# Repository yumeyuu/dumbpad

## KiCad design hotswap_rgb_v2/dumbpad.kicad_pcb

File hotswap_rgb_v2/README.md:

# dumbpad - Hotswap - RGB v2 (aka v4.x)

Originally Designed by [deveth0](https://www.github.com/deveth0).  
Modified by [yumeyuuu](https://github.com/yumeyuu) to fits RP2040 core board.   
Compatible board is [Rpi Pico](https://www.raspberrypi.com/documentation/microcontrollers/raspberry-pi-pico.html) or its clone.

## Description

Version of the original dumbpad that features Kailh Hotswap Sockets and (optional) RGB per-key lightning.  
Modified with additional EEPROM and OLED Screen

### Revisions

- 4.0 Initial file

#### dumbpad v4.0

#### Renders

### Bill of materials

| Qty   | Component     | Values             | Footprint        | Location      | Remarks                       |
| ---:  | :---          | :---               | :---             | :---          | :---:                         |
| 3     | Capacitor     | CAP 0.1u X7R 16V   | SMD 0603         | C1 - C3       |                               |
| 17    | Diodes        | 1N4148W            | SMD SOD123       | D1 - D17      |                               |
| 2     | LED           | Any Colors         | SMD LED 0603     | DL1, DL2      | Original layer indicator LED  |
| 1     | LED           | Any Colors         | SMD LED 0603     | DL3           | Original Numlock status LED   |
| 16    | LED           | SK6812MINI-E       | SK6812MINI-E     | LED1-LED16    | Optional                      |
| 1     | Processor     | RPi Pico           | Rpi Pico Pads    | M1            |                               |
| 1     | OLED Display  | 0.91" OLED Display | 2.54mm Scoket    | M2            |                               |
| 1     | NMOS          | 2N7002             | SOT-23           | Q1            | SK6812 Logic Level Shifter    |
| 3     | Resistor      | RES 1k             | SMD 0603         | R1 - R3       |                               |
| 1     | Resistor      | RES 0 (jumper)     | SMD 0603         | R4            | Bypass resistor               |
| 5     | Resistor      | RES 10k            | SMD 0603         | R5 - R9       | Optional                      |
| 1     | Encoder       | EC11 Rotary Encoder| 7 pins encoder   | RE_3_1        | Any EC11 Compatible OK        |
| 16    | KB-Socket     | Kailh Socket       | Kailh socket     | S1 - S16      |                               |
| 1     | Push Btn      | Alps SKRK          | ALPS SKRK        | S17           |                               |
| 1     | EEPROM        | 24LC32             | SOIC-8           | U1            |                               |
| 1     | Logic IC      | 74LVC2GU04GW       | SC-70            | U2            | Logic Level shifter           |

## Making the PCB

Submit either the KiCad `.kicad_pcb` or the gerber files to your prefered PCB manufacturer.  
Ensure your preffered PCB manufacturer able to process:
- Track Clearance 0.127 mm (5 mils)
- Track Width 0.127 mm (5 mils)
- Min Hole 0.3 mm 
- PCB size 1.6 mm (Common PCB size)

Prebuild gerber file located on the [gerber](gerber/) folder or file [hotswap_rgb_v2-gerber.zip](hotswap_rgb_v2-gerber.zip)

## Opening the design file

The design was created using KiCad 7.0.10 and should be compatible with later iteration.  
Using old version below 7.0 is not tested and probably not supported or could cause problem on the design.
Some of the footprint were not available on the standard KiCad library and hence available on the folder [dumbpad.pretty](dumbpad.pretty/).

### Notes on soldering

- Note 1:
This version uses SMD component, if You are unfamiliar with SMD component.  
Start with lowest possible temperature where Your solder wire can melt properly, and increase the temperature gradually until its flow easily on the solder pads.  
DON'T use high temperature or prolonged soldering time when doing the soldering. Otherwise, You may damage the component or melt the PCB lamination.  

- Note 2:
When soldering the socket and the LED it is recommended to use 360 degree C or as close as possible to this temperature.  
Especially when using Lead-Free solder alloy, its very critical to use lowest temperature where solder alloy can melt and flow easily.  
On my case 355 degree C is good temperature where the solder wire can melt easily and i have sufficient time to get best solder pads wetting.  

- Note 3:
The SK6812 LED plastic case, is very susceptible to melting! Use small solder tip and touch the PCB pads instead of the LED leads (Hakko BC-2 or similar should be good).  
Sometimes it is hard for solder alloy to wet the SK6812 LED lead frame, don't force high temperature or long soldering time!  
Instead, use some flux or clean the soldering area with IPA beforehand.  
On my build i saw some if some of the lead is not get enough solder wetting but i check with multimeter the soldering seems to be have connection. 
I suspect this due to poor storage of the SK6812 LED. (I just put in on the ESD bag with small desiccant, which probably not enough).  

- Note 4:
The SK6812 LED Pads were modified to include little chamfer to indicate GND Pin (Pin 3).

*WARNING:* 
Take a good look at the the orientation of the LEDs! 
The LED orientation changes with changes of the ROW! 

## Acknowledgements

Some of the footprints are extracted from the awesome [Corne Keyboard](https://github.com/foostan/crkbd) by [Kosuke Adachi](https://github.com/foostan).

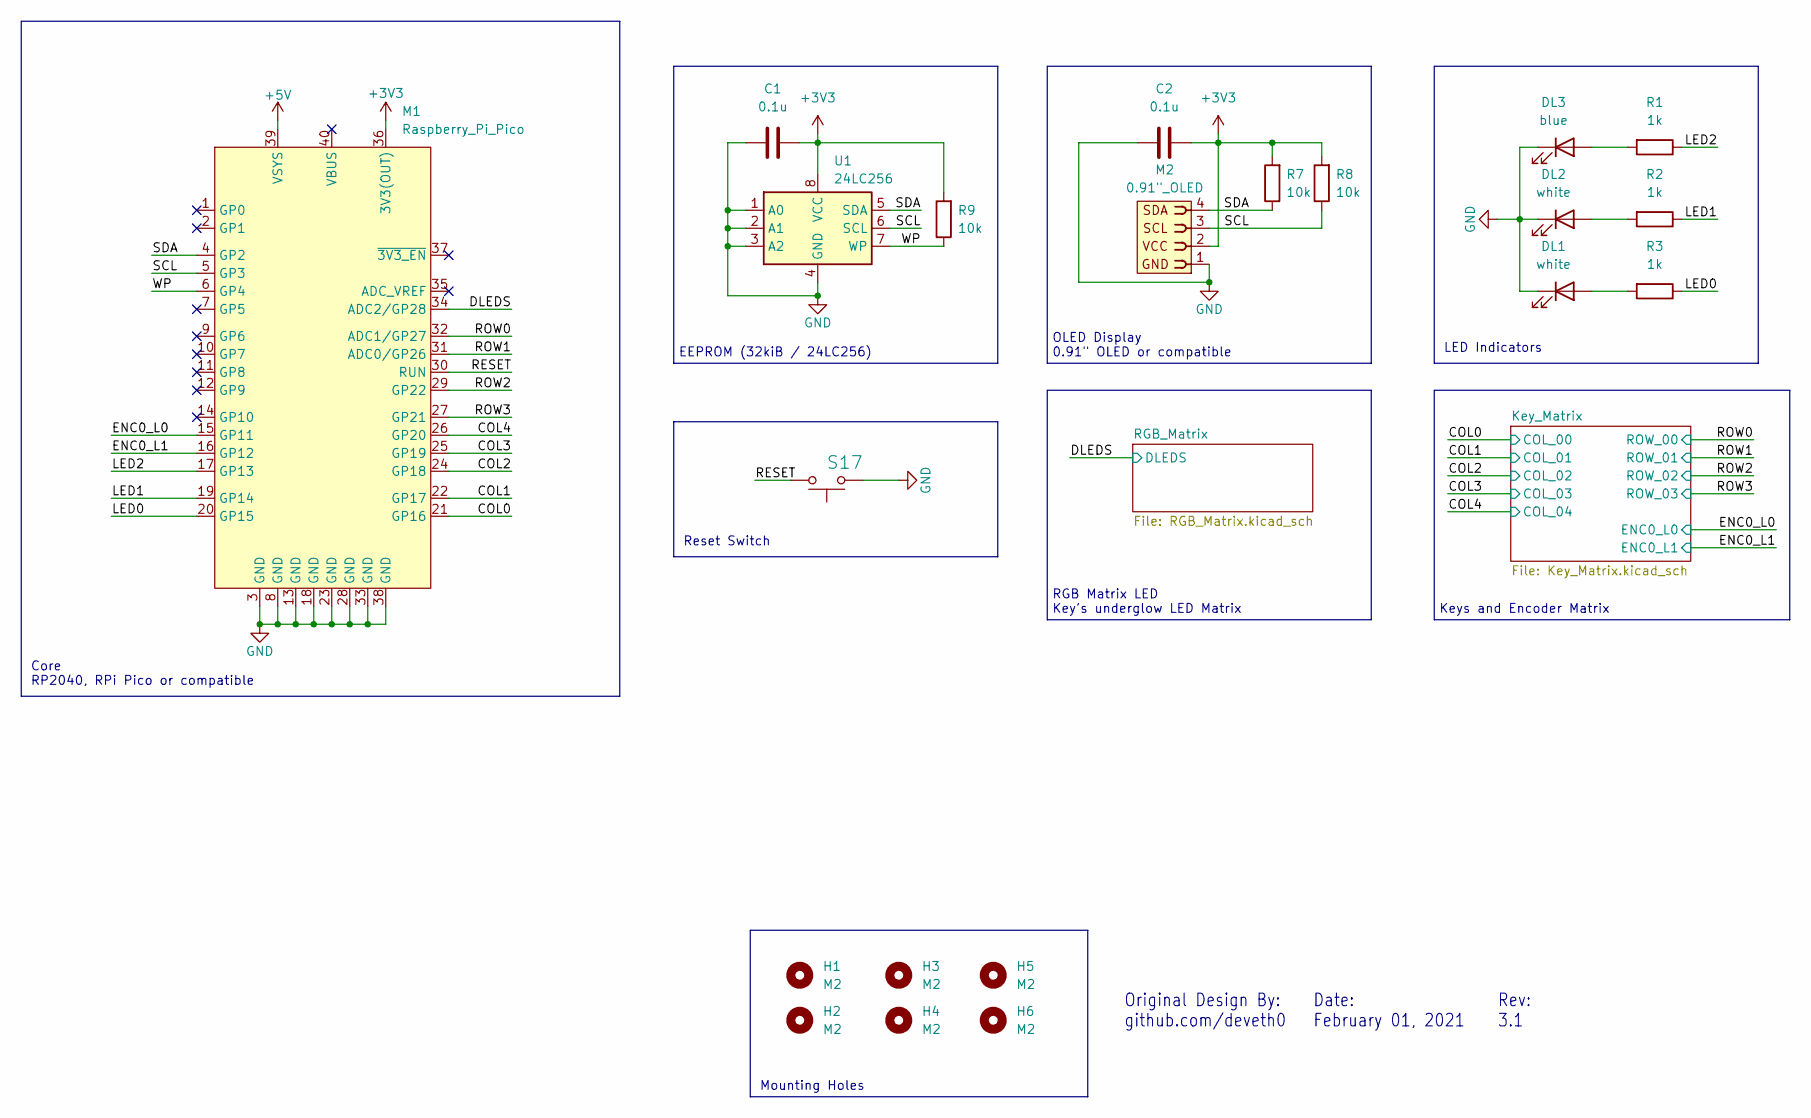
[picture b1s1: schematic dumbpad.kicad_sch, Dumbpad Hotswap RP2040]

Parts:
C1, C2: 0.1u; C_0603_1608Metric
DL1, DL2: white; LED_0603_1608Metric
DL3: blue; LED_0603_1608Metric
H1, H2, H3, H4, H5, H6: M2; MountingHole_2.2mm_M2_DIN965
M1: Raspberry_Pi_Pico; raspberry_pi_pico_THT
M2: 0.91"_OLED; PinSocket_1x04_P2.54mm_Vertical
R1, R2, R3: 1k; R_0603_1608Metric
R7, R8, R9: 10k; R_0603_1608Metric
S17: SPST Push Button; SW_Push_SPST_NO_Alps_SKRK
U1: 24LC256; SOIC-8_3.9x4.9mm_P1.27mm

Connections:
+3V3: C1.1, C2.1, M1.36 (3V3(OUT)), M2.2, R7.2, R8.2, R9.2, U1.8 (VCC); also elsewhere on the board
+5V: M1.39 (VSYS); also elsewhere on the board
/COL0: M1.21 (GP16); also elsewhere on the board
/COL1: M1.22 (GP17); also elsewhere on the board
/COL2: M1.24 (GP18); also elsewhere on the board
/COL3: M1.25 (GP19); also elsewhere on the board
/COL4: M1.26 (GP20); also elsewhere on the board
/DLEDS: M1.34 (ADC2/GP28); also elsewhere on the board
/ENC0_L0: M1.15 (GP11); also elsewhere on the board
/ENC0_L1: M1.16 (GP12); also elsewhere on the board
/LED0: M1.20 (GP15), R3.1
/LED1: M1.19 (GP14), R2.1
/LED2: M1.17 (GP13), R1.1
/RESET: M1.30 (RUN), S17.2
/ROW0: M1.32 (ADC1/GP27); also elsewhere on the board
/ROW1: M1.31 (ADC0/GP26); also elsewhere on the board
/ROW2: M1.29 (GP22); also elsewhere on the board
/ROW3: M1.27 (GP21); also elsewhere on the board
/SCL: M1.5 (GP3), M2.3, R8.1, U1.6 (SCL)
/SDA: M1.4 (GP2), M2.4, R7.1, U1.5 (SDA)
/WP: M1.6 (GP4), R9.1, U1.7 (WP)
GND: C1.2, C2.2, DL1.1 (K), DL2.1 (K), DL3.1 (K), M1.3 (GND), M1.8 (GND), M1.13 (GND), M1.18 (GND), M1.23 (GND), M1.28 (GND), M1.33 (GND), M1.38 (GND), M2.1, S17.1, U1.1 (A0), U1.2 (A1), U1.3 (A2), U1.4 (GND); also elsewhere on the board
unnamed: DL1.2 (A), R3.2
unnamed: DL2.2 (A), R2.2
unnamed: DL3.2 (A), R1.2

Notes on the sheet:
OLED Display 0.91" OLED or compatible
Keys and Encoder Matrix
Rev: 3.1
Core RP2040, RPi Pico or compatible
Original Design By: github.com/deveth0
LED Indicators
RGB Matrix LED Key's underglow LED Matrix
EEPROM (32kiB / 24LC256)
Reset Switch
Mounting Holes
Date: February 01, 2021

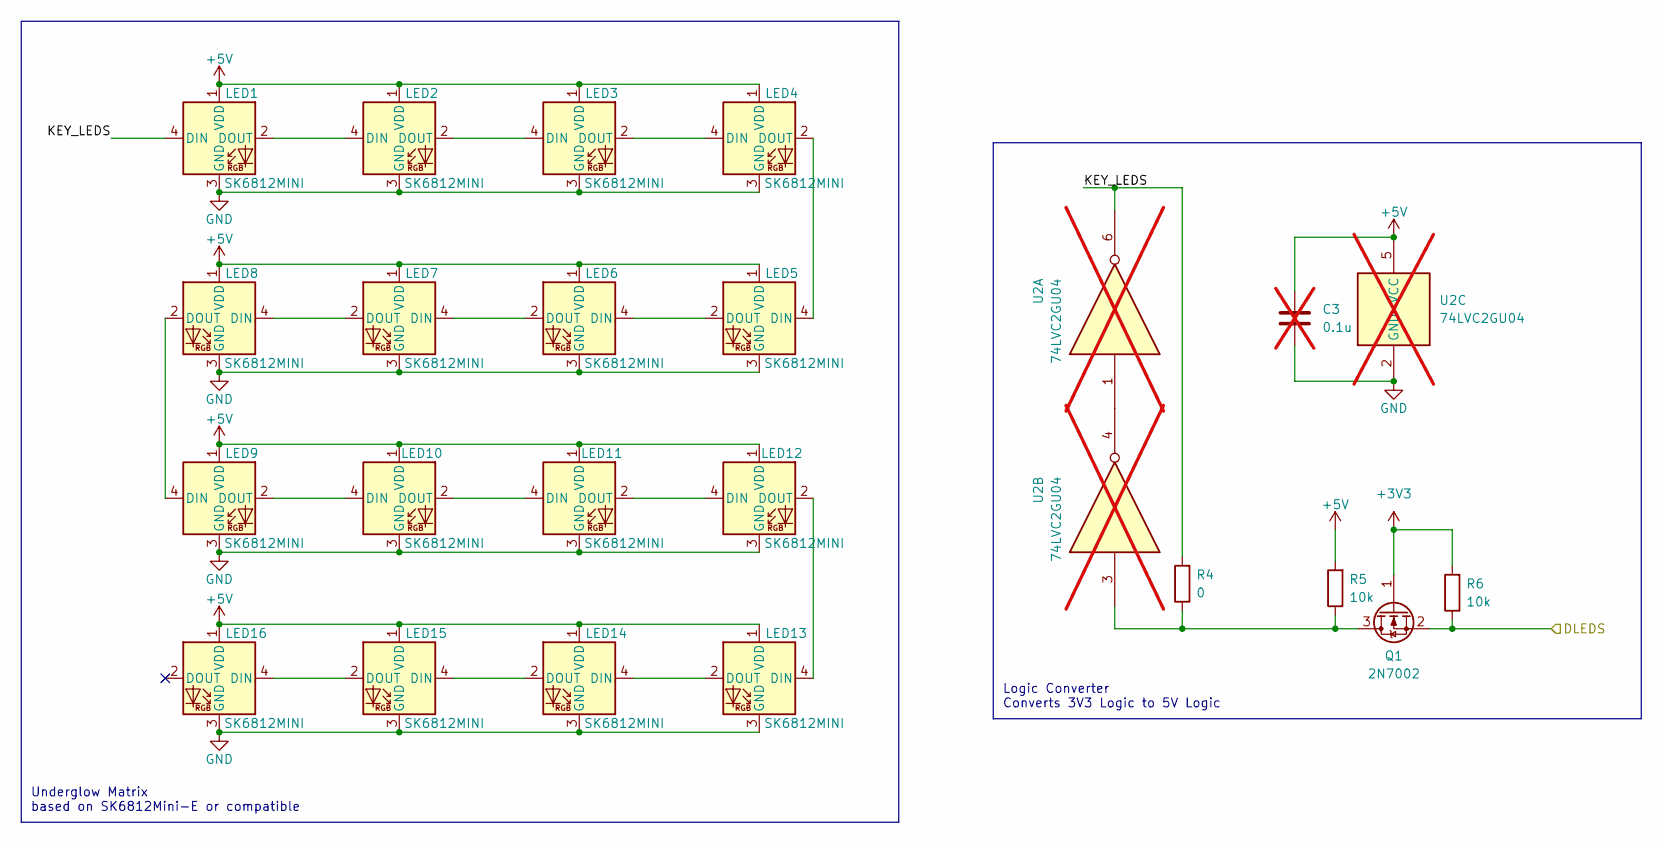
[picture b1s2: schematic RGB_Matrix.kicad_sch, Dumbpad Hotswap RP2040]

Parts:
C3: 0.1u; C_0603_1608Metric; not fitted
LED1, LED2, LED3, LED4, LED5, LED6, LED7, LED8, LED9, LED10, LED11, LED12, LED13, LED14, LED15, LED16: SK6812MINI; YS-SK6812MINI-E
Q1: 2N7002; SOT-23
R4: 0; R_0603_1608Metric
R5, R6: 10k; R_0603_1608Metric
U2: 74LVC2GU04; SOT-363_SC-70-6; not fitted

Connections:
+3V3: Q1.1 (G), R6.2; also elsewhere on the board
+5V: C3.1, LED1.1 (VDD), LED2.1 (VDD), LED3.1 (VDD), LED4.1 (VDD), LED5.1 (VDD), LED6.1 (VDD), LED7.1 (VDD), LED8.1 (VDD), LED9.1 (VDD), LED10.1 (VDD), LED11.1 (VDD), LED12.1 (VDD), LED13.1 (VDD), LED14.1 (VDD), LED15.1 (VDD), LED16.1 (VDD), R5.2, U2.5 (VCC); also elsewhere on the board
/DLEDS: Q1.2 (S), R6.1; also elsewhere on the board
/RGB_Matrix/KEY_LEDS: LED1.4 (DIN), R4.2, U2.6
GND: C3.2, LED1.3 (GND), LED2.3 (GND), LED3.3 (GND), LED4.3 (GND), LED5.3 (GND), LED6.3 (GND), LED7.3 (GND), LED8.3 (GND), LED9.3 (GND), LED10.3 (GND), LED11.3 (GND), LED12.3 (GND), LED13.3 (GND), LED14.3 (GND), LED15.3 (GND), LED16.3 (GND), U2.2 (GND); also elsewhere on the board
unnamed: LED1.2 (DOUT), LED2.4 (DIN)
unnamed: LED2.2 (DOUT), LED3.4 (DIN)
unnamed: LED3.2 (DOUT), LED4.4 (DIN)
unnamed: LED4.2 (DOUT), LED5.4 (DIN)
unnamed: LED5.2 (DOUT), LED6.4 (DIN)
unnamed: LED6.2 (DOUT), LED7.4 (DIN)
unnamed: LED7.2 (DOUT), LED8.4 (DIN)
unnamed: LED8.2 (DOUT), LED9.4 (DIN)
unnamed: LED9.2 (DOUT), LED10.4 (DIN)
unnamed: LED10.2 (DOUT), LED11.4 (DIN)
unnamed: LED11.2 (DOUT), LED12.4 (DIN)
unnamed: LED12.2 (DOUT), LED13.4 (DIN)
unnamed: LED13.2 (DOUT), LED14.4 (DIN)
unnamed: LED14.2 (DOUT), LED15.4 (DIN)
unnamed: LED15.2 (DOUT), LED16.4 (DIN)
unnamed: Q1.3 (D), R4.1, R5.1, U2.3
unnamed: U2.1, U2.4

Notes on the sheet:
Logic Converter Converts 3V3 Logic to 5V Logic
Underglow Matrix based on SK6812Mini-E or compatible

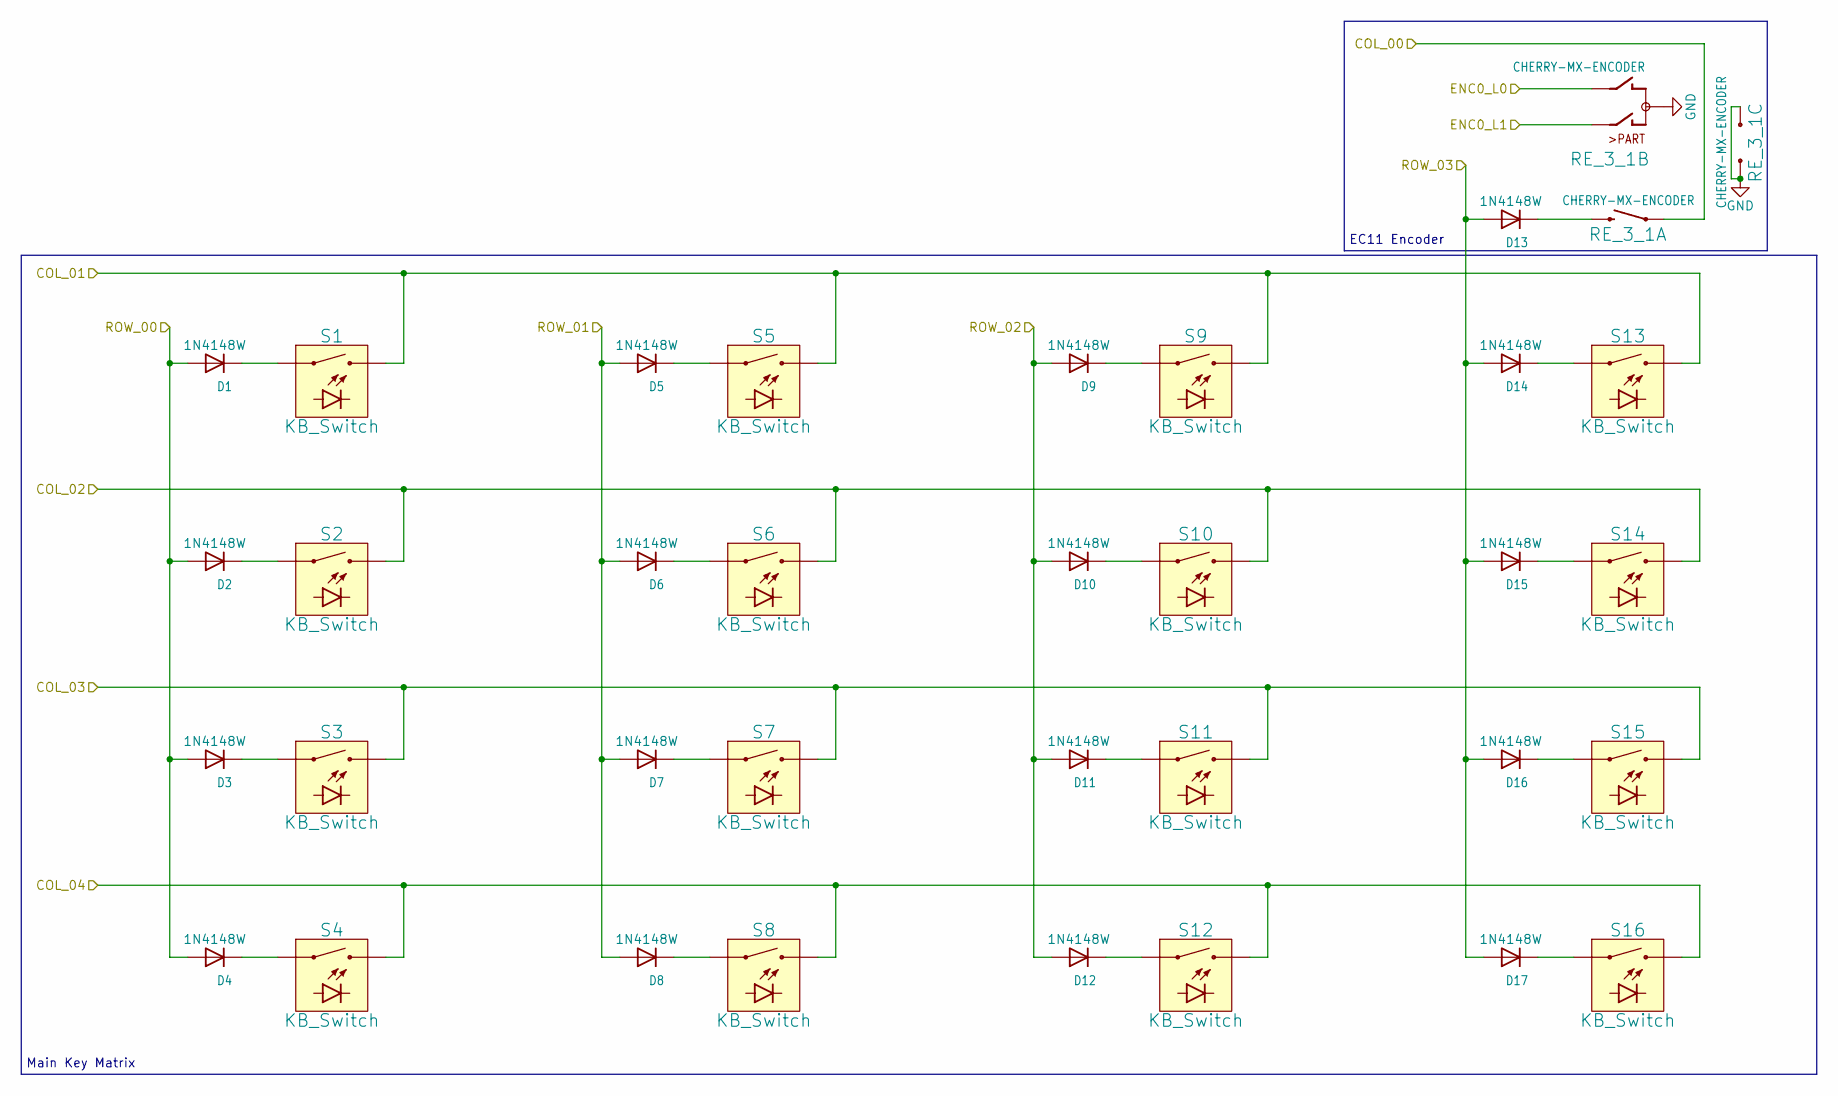
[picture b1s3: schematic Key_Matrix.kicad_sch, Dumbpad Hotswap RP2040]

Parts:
D1, D2, D3, D4, D5, D6, D7, D8, D9, D10, D11, D12, D13, D14, D15, D16, D17: 1N4148W; D_SOD-123
RE_3_1: CHERRY-MX-ENCODER; RotaryEncoder_Alps_EC11E-Switch_Vertical_H20mm
S1, S2, S3, S4, S5, S6, S7, S8, S9, S10, S11, S12, S13, S14, S15, S16: KB_Switch; Kailh-CPG151101S11_MX_Socket-1.00u

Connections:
/COL0: RE_3_1.S1; also elsewhere on the board
/COL1: S1.S2 (2), S5.S2 (2), S9.S2 (2), S13.S2 (2); also elsewhere on the board
/COL2: S2.S2 (2), S6.S2 (2), S10.S2 (2), S14.S2 (2); also elsewhere on the board
/COL3: S3.S2 (2), S7.S2 (2), S11.S2 (2), S15.S2 (2); also elsewhere on the board
/COL4: S4.S2 (2), S8.S2 (2), S12.S2 (2), S16.S2 (2); also elsewhere on the board
/ENC0_L0: RE_3_1.B; also elsewhere on the board
/ENC0_L1: RE_3_1.A; also elsewhere on the board
/ROW0: D1.2 (A), D2.2 (A), D3.2 (A), D4.2 (A); also elsewhere on the board
/ROW1: D5.2 (A), D6.2 (A), D7.2 (A), D8.2 (A); also elsewhere on the board
/ROW2: D9.2 (A), D10.2 (A), D11.2 (A), D12.2 (A); also elsewhere on the board
/ROW3: D13.2 (A), D14.2 (A), D15.2 (A), D16.2 (A), D17.2 (A); also elsewhere on the board
GND: RE_3_1.C, RE_3_1.MP; also elsewhere on the board
unnamed: D1.1 (K), S1.S1 (1)
unnamed: D2.1 (K), S2.S1 (1)
unnamed: D3.1 (K), S3.S1 (1)
unnamed: D4.1 (K), S4.S1 (1)
unnamed: D5.1 (K), S5.S1 (1)
unnamed: D6.1 (K), S6.S1 (1)
unnamed: D7.1 (K), S7.S1 (1)
unnamed: D8.1 (K), S8.S1 (1)
unnamed: D9.1 (K), S9.S1 (1)
unnamed: D10.1 (K), S10.S1 (1)
unnamed: D11.1 (K), S11.S1 (1)
unnamed: D12.1 (K), S12.S1 (1)
unnamed: D13.1 (K), RE_3_1.S2
unnamed: D14.1 (K), S13.S1 (1)
unnamed: D15.1 (K), S14.S1 (1)
unnamed: D16.1 (K), S15.S1 (1)
unnamed: D17.1 (K), S16.S1 (1)

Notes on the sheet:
Main Key Matrix
EC11 Encoder

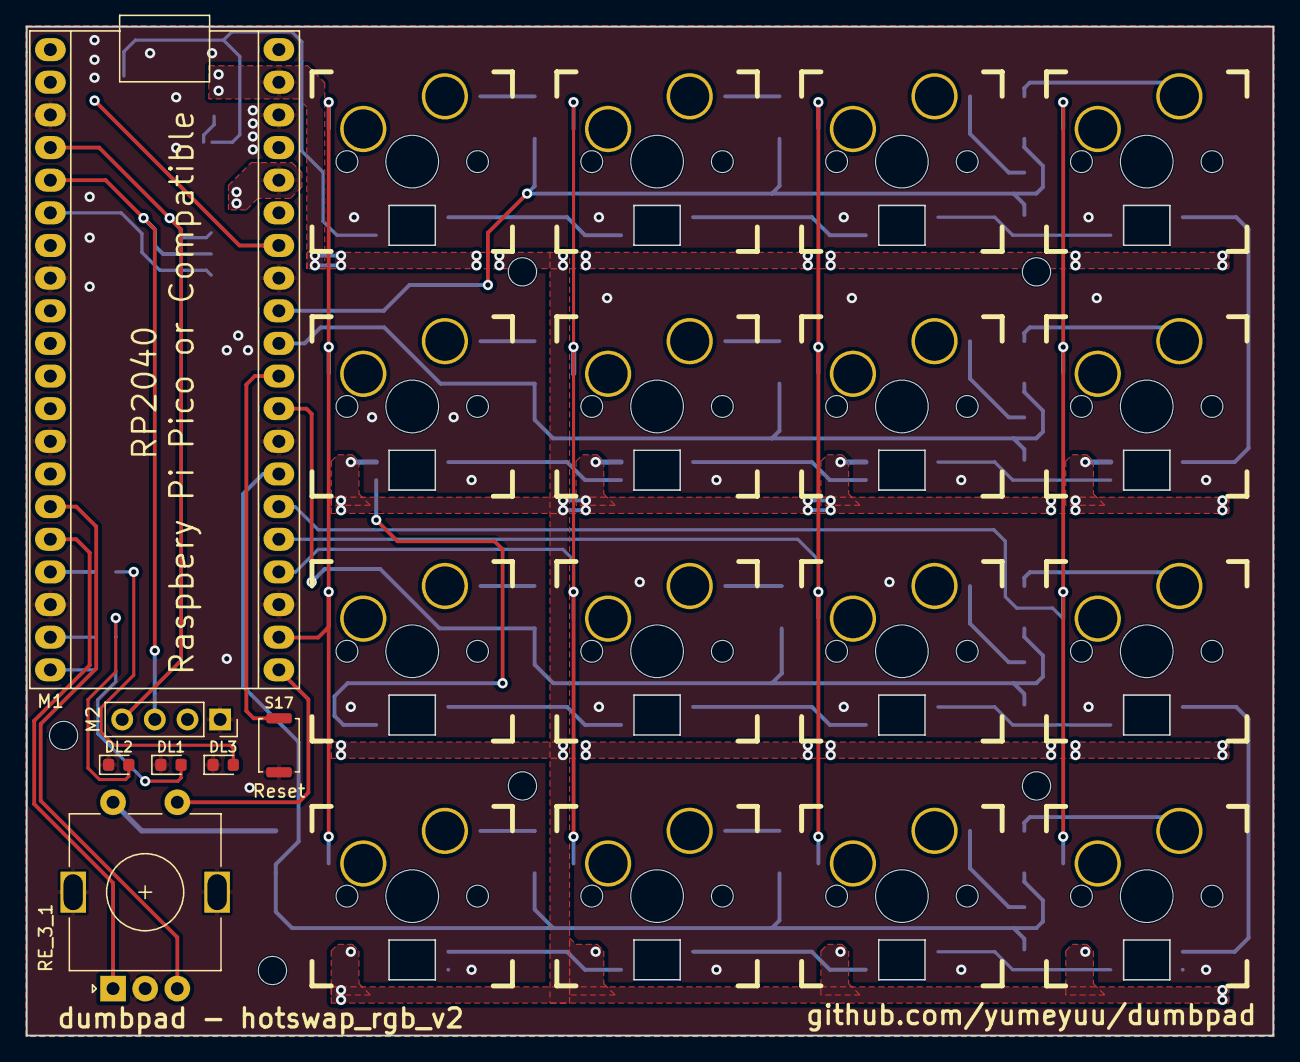
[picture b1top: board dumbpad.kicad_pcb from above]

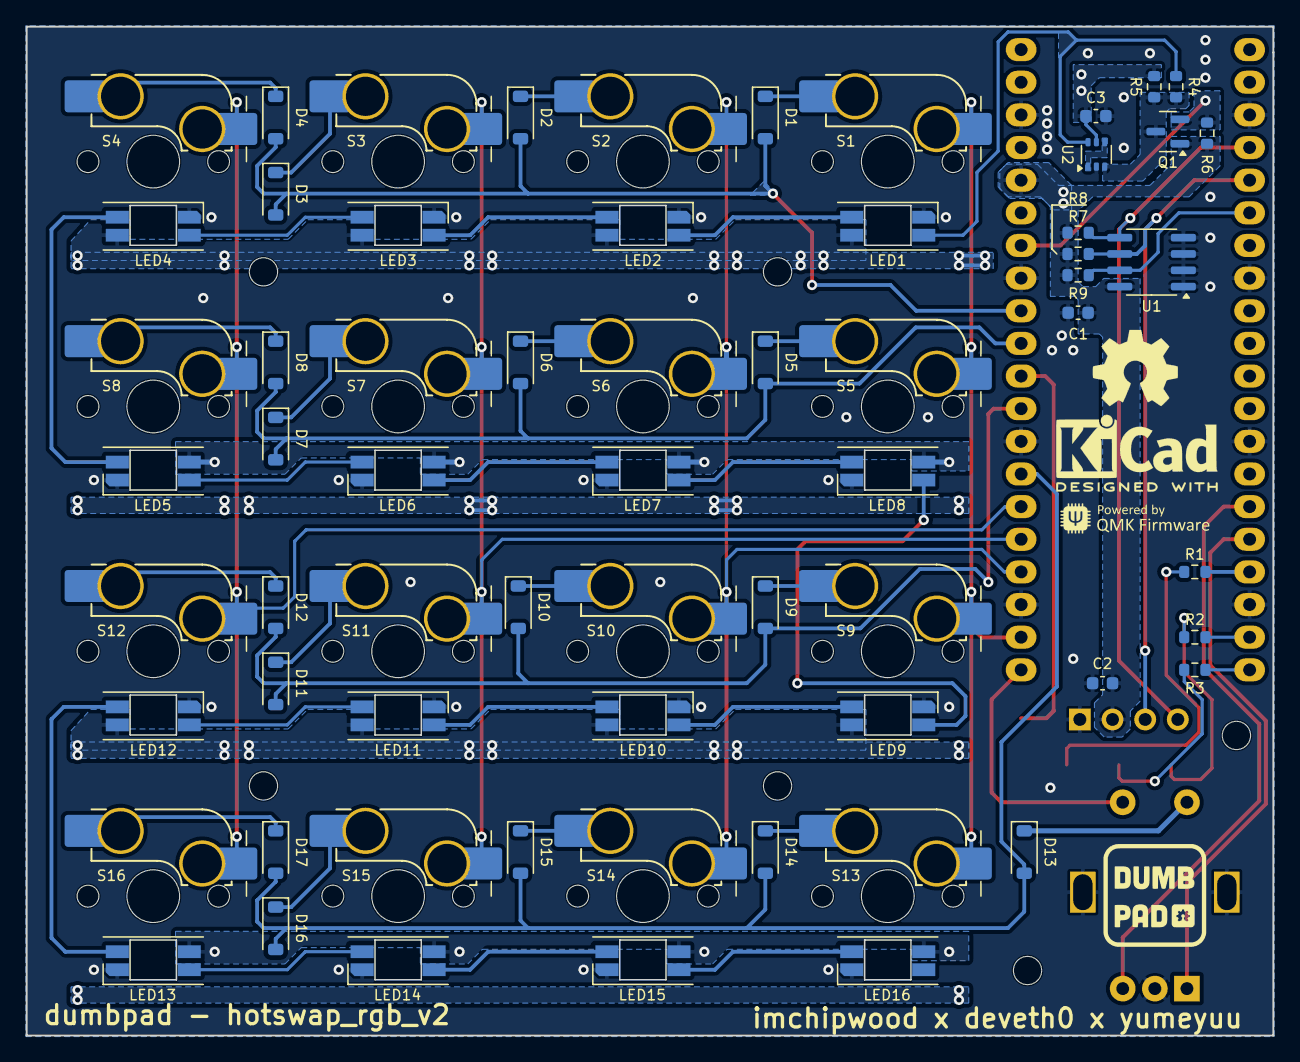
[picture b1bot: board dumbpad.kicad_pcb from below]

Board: 2 copper layers, 97.0 x 78.5 mm, 78 parts (49 on the bottom side), 60 nets.

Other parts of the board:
G1: KiCad-Logo2_5mm_SilkScreen

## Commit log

2024-03-14 initial upload for dumbpad with RPi Pico Core
    Uploading initial modified version of hotswap_rgb with RPi Pico Core.
    initial testing build
2024-08-22 Correct Readme documentation
    Update and correct error on the readme documentation
